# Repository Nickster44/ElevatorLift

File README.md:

# Elevator Lift Controller Redesign

This repository contains the Rev-A hardware design and inhibited software for a redesigned outdoor elevator lift controller. The original controller was a Particle Xenon sketch that drove an EM01 VFD over serial, watched a safety loop, counted position pulses in firmware, stored floor positions in EEPROM, and exchanged simple serial messages with a secondary relay/input board.

The new design goals are:

- Make motion control deterministic and auditable with an explicit state machine.
- Move encoder counting out of interrupt-heavy application code and into a quadrature counter IC.
- Store current position, floor targets, calibration values, faults, and event logs in nonvolatile MRAM.
- Host a local access-point web interface for setup, diagnostics, data logs, and maintenance actions, with optional station-mode connection to a local network.
- Keep safety functions electrically independent from the MCU wherever possible.
- Develop the custom controller board alongside a versioned firmware interface contract.

Important: this repository is not a certified elevator controller. The software here is a development baseline. Any real lift must use appropriately rated safety devices, hardwired interlocks, braking/enable circuits, limit switches, emergency stop hardware, enclosure design, and professional review before operation.

## Software Integration Status (2026-09-13)

The active software is a **buildable but hardware-inhibited N16R8 profile**.
GPIO35-37 are unavailable on this module. The 2026-09-13 hardware update moves
LIMIT_UP/LIMIT_DOWN/SERVICE_KEY to GPIO43/44/3 and makes GPIO42 a communications-only
UART enable, removing the MCU RUN and optional AUX circuits. Software contract v2
now adopts this revision. GPIO3 is input-only, UART0 application logging is disabled,
and UART1 supports STOP/monitor/readback while safety is open. RUN, drive writes,
motion and uploads remain inhibited. Stable input levels do not prove wire continuity.
No physical motion or hardware verification has been performed.

VFD communication now includes periodic STOP refresh (300 ms scheduled interval),
monitor/read traffic, and a separate bounded reply-retry policy. The drive's TIME
watchdog is read and reported, never automatically changed; communication failure
keeps STOP refresh active without restarting motion or clearing faults.

The manual-release STOP path is now target-bound: key/hold/direction release or
invalid direction/safety input queues STOP before ordinary work. Input intent is
reported separately from actual motion permission. The requested operational v3
profile, RF programming and calibration expansion are not complete; v2 remains inhibited.

See the [hardware change and routing handoff](docs/reviews/2026-09-13-pin-comms-fourlayer.md).
The PCB is synchronized and has four copper layers, but remains unrouted and
not layout-release/fabrication ready; isolation keepouts and fabricator-specific
stackup/USB geometry still need completion.

Start with the [software integration checklist](docs/software-integration-checklist.md),
[hardware-dependency handoff](docs/hardware-dependency-handoff.md),
[firmware guide](firmware/README.md) and [current API contract](webapp/docs/api-contract.md).
Portable motion/protocol/device logic has regression tests; target commissioning,
RF integration and several guarded API workflows remain incomplete. The WebUI
shows unavailable capabilities instead of simulating successful hardware actions.

## Current Repository Layout

Use the [documentation guide](docs/README.md) to distinguish current design
guidance from dated reviews and historical evidence.

```text
_old_resources/
  old_code.ino.txt                 Original Particle Xenon firmware
  EM01 Manual User_EN-V1.02.pdf     VFD manual; serial protocol starts on page 27
  SKF-Motor-Encoder-Unit---15276_1-EN.pdf
docs/
  hardware-requirements-matrix.md   Schematic-facing hardware requirements
  hardware-selection.md             Selected Rev-A hardware
  home-automation-integration.md    Local REST/Home Assistant/Google Home bridge plan
  jlcpcb-lcsc-sourcing.md           JLCPCB/LCSC-oriented major part matrix
  motion-control-and-calibration.md Motion strategy and measured stop calibration
  old-system-review.md              Existing firmware/hardware behavior and risks
  vfd-serial-protocol.md            Extracted EM01 serial protocol notes
  new-controller-requirements.md    Hardware and firmware requirements draft
  webui-vfd-and-storage-plan.md     WebUI, VFD parameter, and log storage plan
  webapp-embedded-delivery.md       ESP32 static bundle budget and serving rules
  field-verification-log.md         Observed legacy hardware and remaining site checks
  schematic-capture-readiness.md    Rev-A capture inputs, BOM register, and release gates
datasheets/
  README.md                         Local datasheet manifest for major ICs/modules
firmware/
  platformio.ini                    Inhibited N16R8 PlatformIO target
  include/
  src/
webapp/
  app/                              Full development and service-console UI
  embedded/                         Static entry point for the ESP32 build
  docs/                             WebUI API, safety, and delivery contracts
hardware/
  ElevatorLift.kicad_pro            KiCad 10 project; open this file
  ElevatorLift.kicad_sch            Root hierarchical schematic
  Power_RevA.kicad_sch              AC input and 12 V/5 V/3.3 V power
  MCU_Storage_RevA.kicad_sch        ESP32-S3, USB, MRAM and RTC
  VFD_Interface_RevA.kicad_sch      VFD UART and communications-only OE
  Encoder_Counter_RevA.kicad_sch    Encoder isolation and counter
  IO.kicad_sch                      RF, field inputs and outputs
  ElevatorLift.kicad_pcb            PCB WIP; full footprint/net transfer on a 90 mm x 90 mm outline with 86 mm hole centers
  ElevatorLift_Custom.kicad_sym     Project-owned symbols
  ElevatorLift_Custom.pretty/       Project-owned footprints
  SnapEDA-Library/                  Vendored imported symbols, footprints and STEP files
  sym-lib-table / fp-lib-table      Portable project library registrations
  architecture-blocks.md            Block-level hardware architecture notes
```

## Current Design Knowledge

The current hardware direction is an `ESP32-S3-WROOM-1U-N16R8` controller board in the VFD enclosure, using a self-hosted Wi-Fi AP as the primary service path and optional station Wi-Fi for local-network access. Ethernet is not a near-term requirement.

Known design constraints captured so far:

- KiCad 10.0.4 is the active hardware design version.
- Measured legacy mechanical target is approximately 90 mm x 90 mm with corner mounting-hole centers 86 mm apart; 2.56 mm hole diameter remains to be confirmed.
- The Rev-A VFD serial circuit has been cross-checked against the field design and reproduces its TI `TXS0104E` 3.3 V-to-5 V topology. The assembled board, connector pinout, reference, and idle levels still require bench verification before lift connection.
- The observed encoder path appears to be 12 V open-collector A/B with 270 ohm pullups and 270 ohm series resistors feeding a `TLP291-4` optocoupler. Trace details, current, and maximum pulse rate remain open.
- Legacy Linx/TE RXM-418-LR 418 MHz RF remote support is mandatory.
- Baseline control supply is RECOM `RAC10-12SK/277`, 12 V, 10 W, based on the previously observed installation; `C5199922` is a recorded sourcing reference, not verified current availability.
- Rev A retains a jumper-selectable external 12 V lighting input. Use it if measured controller margin is insufficient or future lighting requires more power than the onboard supply can provide.
- Critical state and recent logs should use 4 Mbit SPI/QPI MRAM, using the selected Siproin `PM004MNIATR`.
- Web assets, OTA staging and noncritical logs should use the module's 16 MB flash and 8 MB PSRAM first. Rev A does not include a separate QSPI NOR device.
- Outside control should use local REST first, optional MQTT later, and Home Assistant as the recommended bridge to Google Home, watches, and broader automation.
- Motion control should use measured deceleration-distance stopping, not PID. Planned calibration starts explicitly after valid floor programming and stores direction-specific offsets; target integration remains incomplete.

## Legacy Reference

The original pin map, behavior and risk analysis are retained in
[old-system-review.md](docs/old-system-review.md). They are historical evidence,
not wiring or operating instructions for Rev A.

## Firmware Direction

The firmware targets the exact N16R8 module using Arduino/PlatformIO and a versioned hardware interface contract. Portable core logic is tested separately from target adapters. A successful build is not permission to deploy.

Key modules:

- `core/Supervisor`: fault-latched motion, service, homing and measured calibration logic.
- `core/Em01`, `DriveScheduler`: framed/checksummed transactions, telemetry and readback.
- `core/Devices`, `Configuration`: LS7366R, PM004 MRAM, RTC and integrity-checked records.
- `core/Rf`: isolated learned-slot/epoch and input arbitration logic.
- `main.cpp`: inhibited target diagnostics, light output, networking and static hosting.
- `interface-contract.json`: confirmed pins and explicit unresolved hardware decisions.

## Local Web Interface/API

The firmware hosts static WebUI assets on port 80 and a fallback AP. Station credentials can be saved, but remote reboot is deliberately unsupported in the inhibited profile. Failed/lost station connectivity restores AP access. Blank API tokens disable writes.

Endpoints:

- `GET /` - embedded WebUI; no automatic demo mode.
- `GET /api/status` - versioned status, capabilities, blocked reasons and freshness.
- `GET /api/capabilities` - explicit supported capabilities.
- `GET /api/network` - current AP/station network status.
- `POST /api/network` - save station SSID/password and require a reboot.
- `POST /api/light` - idempotent light output command.
- `GET /api/logs/recent` - bounded durable MRAM events, unavailable on storage failure.
- `GET /api/vfd/parameters` - list documented VFD parameter metadata.
- `POST /api/move?floor=N` - strict input validation, then hardware-inhibited rejection.
- `POST /api/stop` - queues diagnostic STOP (202), or reports unavailable UART (503); neither transmission nor acknowledgement proves physical stopping.

Other commissioning, parameter-write, RF, restore and reboot endpoints are explicitly unsupported. See the API contract for remaining work; no UI capability implies hardware verification.

Fallback AP credentials are configured from `firmware/include/Secrets.h`, which is ignored by Git. Station network credentials are saved through the local web API.

Planned WebUI expansion includes local lift settings, RF pairing, VFD parameter read/write, current-limit/load-limit tuning, configuration backup/restore, and log export.

The preferred home-automation path is local REST API first, optional MQTT later, and Home Assistant as the bridge to Google Home. Google Home should not talk directly to the lift controller or bypass the controller's authentication, logging, and motion prechecks.

## Captured Hardware Architecture

The Rev-A design contains the following blocks; physical qualification remains open:

- Exact `ESP32-S3-WROOM-1U-N16R8` external-antenna Wi-Fi module.
- Fused 120 VAC + neutral input, isolated 12 V supply, 5 V rail, and 3.3 V rail.
- VFD UART interface reproducing the field-used 3.3 V-to-5 V `TXS0104E` topology, with an assembled-board bench gate before lift connection.
- LS7366R SPI quadrature counter.
- Encoder input conditioning for the observed 12 V open-collector quadrature outputs, including isolation/level translation before the counter.
- SPI MRAM for live position snapshots, settings, recent event logs, and fault records.
- The selected N16R8 module's 16 MB flash and 8 MB PSRAM serve WebUI assets, OTA staging and noncritical data; no separate Rev-A QSPI device is planned.
- Hardware safety chain independent of application firmware.
- External hardwired motion authority; GPIO42 enables UART translation only, not RUN or a brake.
- Protected digital inputs for call buttons, RF receiver, limit switches, home switch, and safety loop.
- Mandatory RXM-418-LR RF receiver path.
- Protected 12 V MOSFET light output with jumper-selectable onboard or external 12 V supply. AUX has been removed.
- Watchdog and brownout detection.
- Surge/ESD/EMI protection suitable for outdoor wiring and a VFD enclosure.

The service/recovery interface uses dry-contact inputs: J43 provides SERVICE
KEY, HOLD-TO-RUN and GND; J44 provides SERVICE UP, SERVICE DOWN and GND. The
intended external hardware is a maintained keyed service switch, a momentary
hold-to-run control, and momentary UP/DOWN controls. These optocoupler-conditioned, shared-ground
MCU inputs are authorization/command inputs only; they are not a safety-rated
enabling circuit and may not bypass the independent emergency-stop, final-limit,
watchdog or VFD motion-authority paths.

## Opening The Hardware Project On Another Computer

Clone or copy the complete repository and open `hardware/ElevatorLift.kicad_pro`
with KiCad 10. The custom and SnapEDA libraries are stored under `hardware/` and
registered through `${KIPRJMOD}` paths, so no `D:\Downloads` or user-profile
library path is required. Do not copy only the `.kicad_pro` file: the five child
schematics, board, project library tables, custom libraries and vendored
SnapEDA library directory must remain together.

## Physical Verification Checklist

The initial on-site observations are recorded in `docs/field-verification-log.md`.
Before hardware release, complete the remaining checks below. The
[external-box evidence checklist](docs/reviews/2026-09-13-manual-control-box.md)
defines the non-energized wiring review; this list does not authorize live testing.

1. Confirm the estimated 40 mm enclosure height and 12 mm underside clearance, then measure connector/wire-bend keepouts and airflow.
2. Confirm the approximately 90 mm x 90 mm board, 86 mm mounting-hole centers, 2.56 mm hole diameter, screw size, and standoff material.
3. Old controller hardware: photograph both sides of the Particle/Xenon board and accessory Nano board, record IC markings, regulator parts, RF receiver wiring, level-shifting parts, optocouplers, drivers, relay part numbers, fuses, MOVs, terminal blocks, and any bodge wiring.
4. VFD serial interface: verify the field-matched `TXS0104E` circuit on the assembled board, including header pinout, idle voltage, common/reference, polarity, receive level, cable length, and bench behavior.
5. Power input: where 120 VAC can be tapped, whether it is upstream/downstream of the disconnect, available neutral, protective earth/chassis connection, fuse location, wire gauge, and connector style.
6. Existing 12 V loads: light voltage/current, inrush behavior, shared return path, connector type, and whether any solenoid/interlock output still needs power.
7. Encoder wiring: verify the observed 12 V supply, 270 ohm pullups, 270 ohm series resistors, `TLP291-4` path, exact encoder model, A/B idle voltage, cable/shielding, connector pinout, and maximum pulse rate.
8. Button, home, limit, and safety wiring: voltage levels, normally-open/normally-closed behavior, whether contacts are dry or powered, cable routing, and what is hardwired versus MCU-only.
9. RF system: confirm receiver module marking, antenna type/location, data output idle level, remote count, remote mapping, pairing behavior, and the separate wired `LEARN` node.
10. Grounding and EMI: cabinet earth strategy, shield terminations, VFD motor lead routing, separation between mains/motor wiring and control wiring, and any existing noise filters.
11. VFD parameters: dump or photograph current drive parameters, especially acceleration, deceleration, max frequency, current/overload settings, serial timeout, and any stop/enable terminal configuration.
12. Safety devices: identify final limits, emergency stop, gate/latch devices, brakes, and any non-MCU circuits that remove motion authority.

## Remaining Software Work

Drivers, integrity-checked MRAM records, token authentication and host protocol
simulations exist. Track remaining operational motion, RF capture/programming,
explicit calibration, guarded settings and update workflows in the
[integration checklist](docs/software-integration-checklist.md).

## Build Firmware Without Deployment

Install PlatformIO, then run:

```powershell
cd firmware
pio run
```

Upload and uploadfs deliberately fail in this profile. See the
[firmware guide](firmware/README.md) for host tests and filesystem builds and the
[WebUI guide](webapp/README.md) for mocked browser tests. Do not remove the inhibit
to try hardware; physical qualification remains separate.

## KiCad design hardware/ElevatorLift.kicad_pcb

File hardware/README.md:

# Hardware / KiCad Workspace

This folder is the hardware design workspace. The KiCad 10 project now contains a Rev-A schematic capture and an unrouted four-layer PCB for review. It is not yet approved for PCB layout or manufacturing.

## Files

| File | Purpose |
| --- | --- |
| `ElevatorLift.kicad_pro` | KiCad project |
| `ElevatorLift.kicad_sch` | Root hierarchical schematic |
| `Power_RevA.kicad_sch` | Fused AC input and isolated 12 V, 5 V and 3.3 V rails |
| `MCU_Storage_RevA.kicad_sch` | ESP32-S3, USB, MRAM, RTC and service interfaces |
| `VFD_Interface_RevA.kicad_sch` | 3.3 V/5 V UART translation; communications-only enable, no MCU RUN output |
| `Encoder_Counter_RevA.kicad_sch` | Isolated encoder inputs and LS7366R counter |
| `IO.kicad_sch` | Linx RF, monitored field inputs and light output; optional AUX removed |
| `ElevatorLift.kicad_pcb` | PCB work-in-progress: 90 mm x 90 mm outline, 86 mm corner-hole centers, and the complete schematic footprint/net transfer |
| `ElevatorLift_Custom.kicad_sym` / `ElevatorLift_Custom.pretty` | Project-owned custom symbols and corrected/provisional footprints |
| `SnapEDA-Library` | Repository-owned copy of imported symbols, footprints and supplied STEP files |
| `sym-lib-table` / `fp-lib-table` | Project library registrations using portable `${KIPRJMOD}` paths |
| `architecture-blocks.md` | Schematic page/block plan |

## Current Schematic Pages

1. Root hierarchy and design notes.
2. Power (`Power_RevA`).
3. MCU and storage (`MCU_Storage_RevA`).
4. VFD interface (`VFD_Interface_RevA`).
5. Encoder counter (`Encoder_Counter_RevA`).
6. Consolidated RF, field inputs and outputs (`IO`).

The superseded standalone RF, safety, output and connector child sheets were
removed after their contents were consolidated into the active Rev-A hierarchy.

## Rev-A Capture Assumptions

Use [the hardware requirements matrix](../docs/hardware-requirements-matrix.md) and the main README physical verification checklist as the source of truth. The current schematic assumptions are:

- Target PCB outline: 90 mm x 90 mm; corner mounting-hole centers 86 mm apart. The reported 12 mm underside and approximately 40 mm upper clearances are enclosure estimates, not defined keepout radii. Verify screw-head/standoff envelopes and the estimated 2.56 mm hole diameter before layout release.
- Main supply: fused 120 VAC + neutral to exact RECOM `RAC10-12SK/277`; protected 12 V distribution uses `MF-MSMF075/24X`; 5 V uses an `R-78E5.0-0.5`; and 3.3 V uses an AP63203 stage with Bourns `SRP7028A-2R2M`.
- 5 V source sharing: separate `LM66100DCKR` ideal diodes isolate the onboard 5 V converter and USB VBUS before they join the 5 V rail. USB VBUS alone does not power the separate 3.3 V regulator; an approved bench-power procedure remains necessary.
- VFD serial: the `TXS0104E` circuit matches the field design, with the `TSW-104-07-G-S` header ordered 5 V, GND, RX, TX. Assembled-board pinout and bench behavior remain release gates.
- Encoder: 12 V field inputs use 2.2 kOhm LED resistors into `TLP291-4` isolation. This intentionally replaces the observed legacy 270 ohm values to avoid excessive optocoupler current; verify reliable switching on the actual encoder.
- RF: RXM-418-LR and `LICAL-DEC-MS001` support is mandatory; include a separate wired `LEARN` interface plus a local service button/pads.
- Light output: protected 12 V MOSFET output with an onboard/external supply selector. The previous 750 mA lighting operated from the 10 W RAC10 supply; verify Rev-A load margin, and select the external 12 V lamp input if controller demand or upgraded lighting exceeds the onboard budget.
- Service station: J43 accepts dry-contact SERVICE KEY and HOLD-TO-RUN inputs with a shared GND; J44 accepts dry-contact SERVICE UP and SERVICE DOWN inputs with a shared GND. Use a maintained key switch and momentary controls. These are optocoupler-conditioned MCU inputs sharing controller GND, not an independent galvanic barrier or a safety-rated enabling circuit.
- Current MCU assignment: LIMIT_UP GPIO43/module pin 37 through 1k R62; LIMIT_DOWN GPIO44/pin 36; SERVICE_KEY GPIO3/pin 15. GPIO35/36/37 remain NC for octal PSRAM. J11 UART pins 3/4 are now NC; use native USB. Preserve active-low inputs and default JTAG eFuses; see the reset/boot details in the current handoff.
- GPIO42 is VFD_COMMS_ENABLE and connects only U24 OE plus R24's 10k pulldown. R25/U25/J25/TP26 and AUX R59/R60/Q41/F41/D42/J47 are removed. The separate external hardwired safety loop remains the required RUN authority, subject to VFD configuration verification.

## PCB Preparation Status

- The current board contains 126 footprints (including four mounting holes) and 140 nets. The 90 x 90 mm outline runs from `(97.26,52.29325)` to `(187.26,142.29325)` mm. The four provisional 2.6 mm NPTH holes retain 86 mm spacing and a 2 mm offset from each adjacent edge.
- Net classes retain 3.2 mm mains clearance and 0.8 mm SELV power track width (0.2 mm clearance), plus the provisional USB differential-pair settings.
- The downloaded ESP32 module footprint contained invalid 0.2 mm plated holes. `ElevatorLift_Custom:ESP32-S3-WROOM-1U-N16R8_CorrectedV2` replaces it with the correct perimeter geometry and nine symbol-compatible exposed-pad segments.
- The provisional mains connector is now Phoenix Contact `1717732`, 7.62 mm pitch. The former 5 mm-pitch part could not satisfy the selected 3.2 mm mains clearance rule.
- Existing footprint positions and sides are preserved except for a local C23/C26 move that shortens U20's input/bootstrap loops; new R62 was also placed. Four layers are enabled: F.Cu, In1.Cu (SELV GND reference), In2.Cu (power/constrained signals), B.Cu. No tracks or zones were created. The nominal 1.6 mm board thickness is not a selected fabricator stackup.
- Current verification: ERC 0 errors/31 unchanged warnings; PCB DRC 325 unrouted errors, 181 warnings, no other errors, zero schematic parity findings. The final Konnect synchronization dry run is a no-op. These checks do not make the board layout-ready.
- See [the current handoff](../docs/reviews/2026-09-13-pin-comms-fourlayer.md) for exact pin mapping, prototype gates, placement concerns, all-layer isolation/antenna keepouts still to implement, and the provisional USB rule. Konnect's `.konnect/project.json` records routing guidance, not enforced KiCad custom rules.

Dated review results are evidence, not a live release status. See the
[external-box review](../docs/reviews/2026-09-13-manual-control-box.md) for the
latest field-interface evidence and unresolved independent stopping authority.

## Portable Project Libraries

Open `ElevatorLift.kicad_pro`, not an individual child sheet. Both project
library tables use `${KIPRJMOD}` paths:

- `SnapEDA` resolves to `hardware/SnapEDA-Library`.
- `ElevatorLift_Custom` resolves to the custom symbol file and footprint folder
  beside the project.

The repository-owned SnapEDA directory is a byte-for-byte copy of the imported
download and includes the supplied STEP files. Standard KiCad libraries are
still required, so install KiCad 10 with its normal symbol and footprint
packages on the destination computer.

See [field observations](../docs/field-verification-log.md) and the
[capture register](../docs/schematic-capture-readiness.md) for the confirmed observations, reusable-parts register, and the remaining release gates.

## KiCad Tooling

This project is pinned to KiCad 10.0.4. Use `tools\kicad.ps1` rather than a
generic `kicad-cli` command so automated checks do not accidentally run against
the also-installed KiCad 8 version.

```powershell
# From the repository root
powershell -ExecutionPolicy Bypass -File hardware\tools\kicad.ps1 -Action Version
powershell -ExecutionPolicy Bypass -File hardware\tools\kicad.ps1 -Action Validate
powershell -ExecutionPolicy Bypass -File hardware\tools\kicad.ps1 -Action Gui
```

`Validate` writes KiCad-native ERC and DRC JSON reports to `hardware\reports`
by default. The reports are generated design-review artifacts and should be
regenerated whenever the schematic or board changes.

The helper scripts auto-detect conventional OneDrive/Documents KiCad plugin
locations. On a different layout, set `KONNECT_PLUGIN_ROOT` to the installed
Konnect directory and `KICAD_10_BIN` to the KiCad 10 `bin` directory. Neither
environment variable is required merely to open and edit the project in KiCad.
Use PowerShell 7 for the Konnect batch helper; the basic KiCad launcher also
supports Windows PowerShell 5.1.

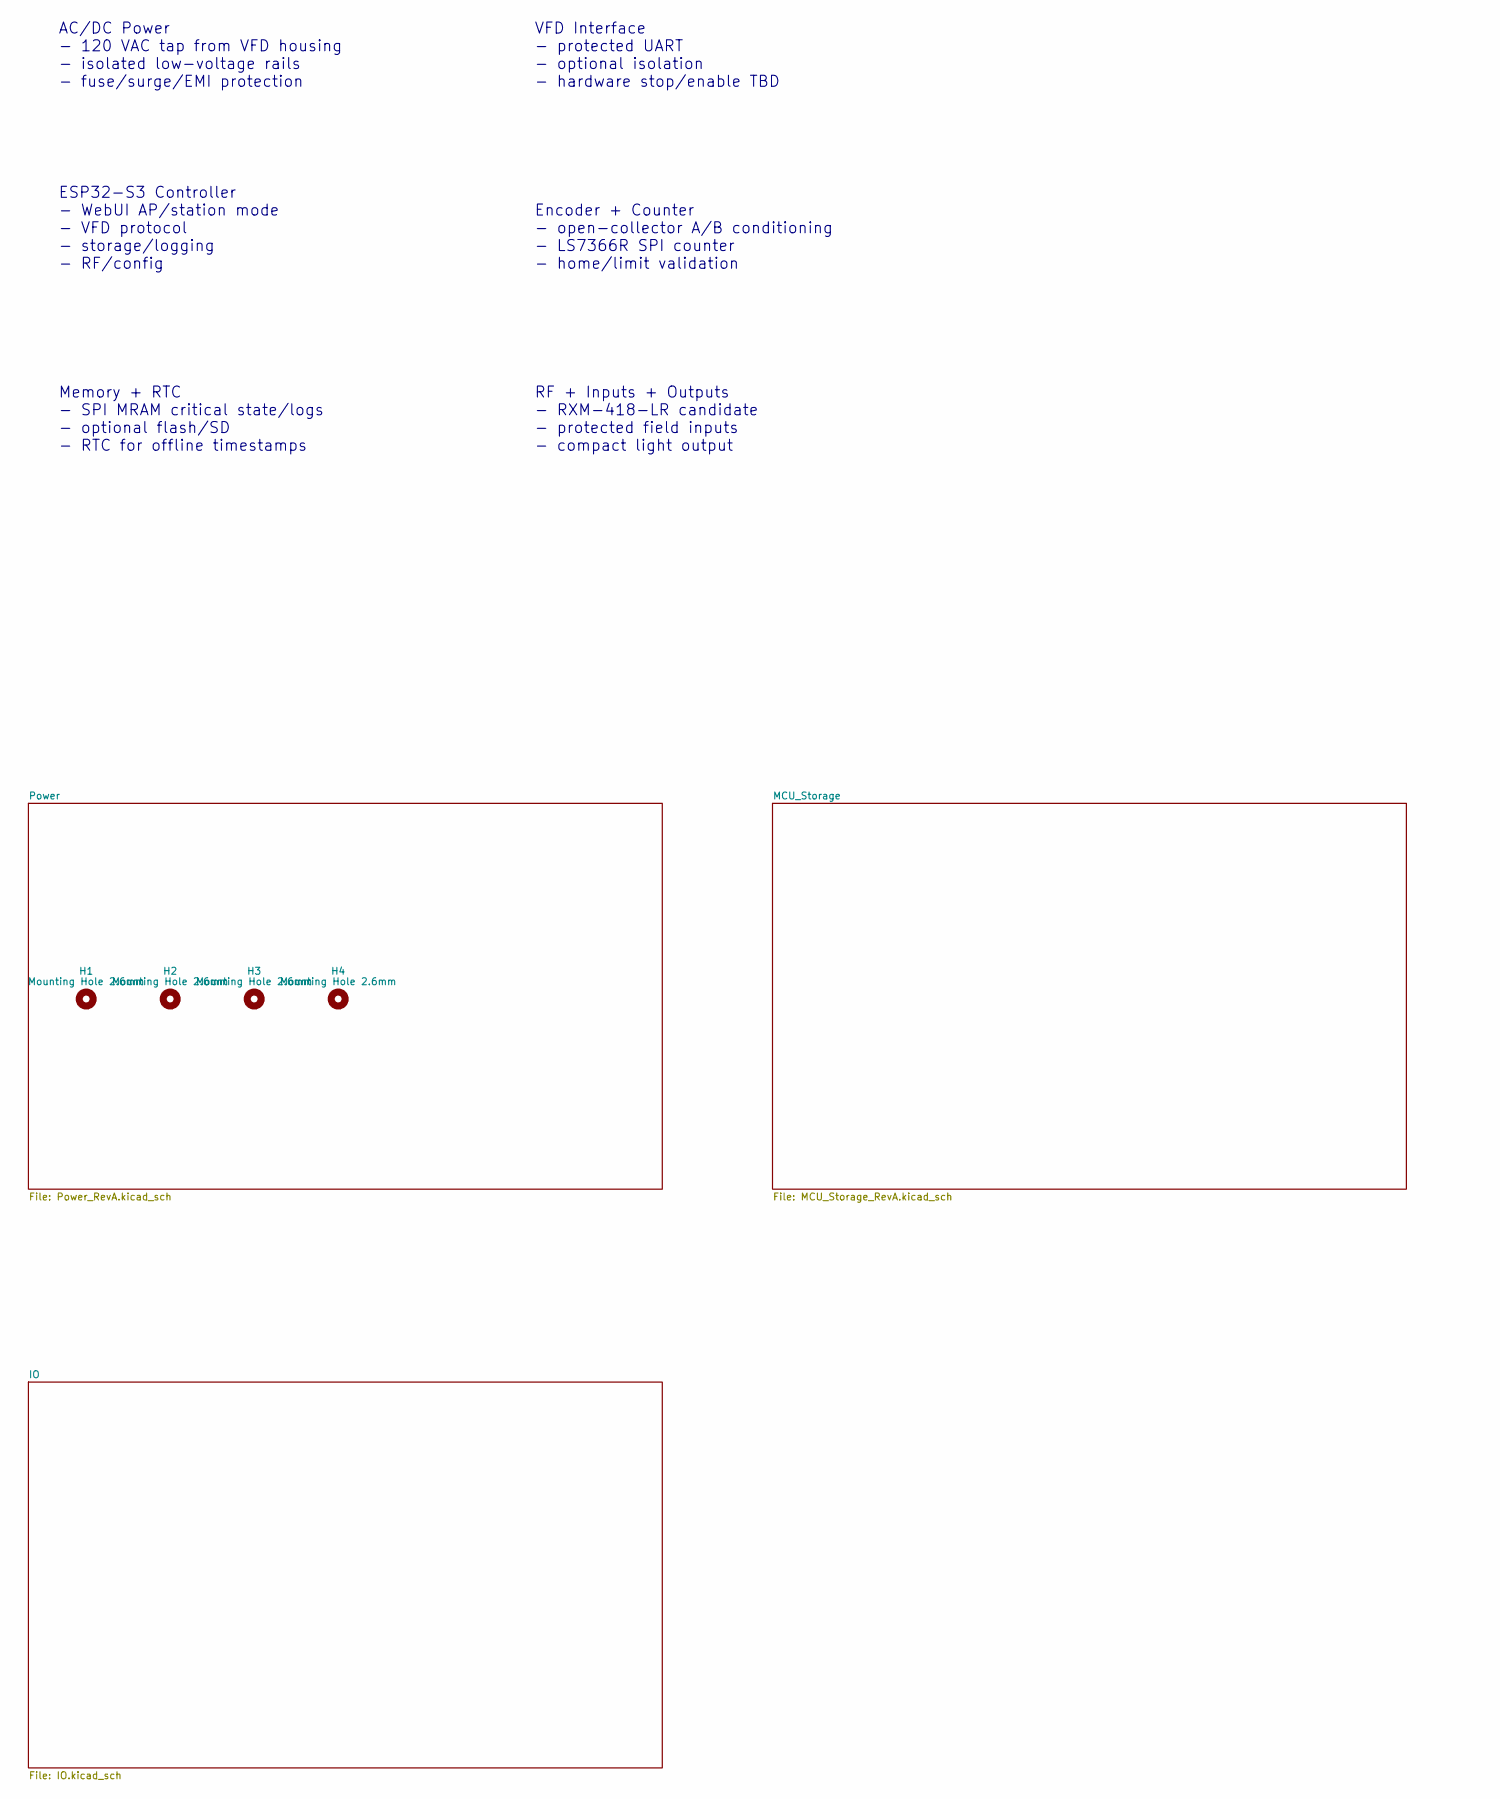
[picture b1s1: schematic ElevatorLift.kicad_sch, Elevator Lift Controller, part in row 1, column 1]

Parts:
H1, H2, H3, H4: Mounting Hole 2.6mm; MountingHole_2.6mm_NPTH

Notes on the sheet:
ESP32-S3 Controller - WebUI AP/station mode - VFD protocol - storage/logging - RF/config
RF + Inputs + Outputs - RXM-418-LR candidate - protected field inputs - compact light output
AC/DC Power - 120 VAC tap from VFD housing - isolated low-voltage rails - fuse/surge/EMI protection
VFD Interface - protected UART - optional isolation - hardware stop/enable TBD
Memory + RTC - SPI MRAM critical state/logs - optional flash/SD - RTC for offline timestamps
Encoder + Counter - open-collector A/B conditioning - LS7366R SPI counter - home/limit validation

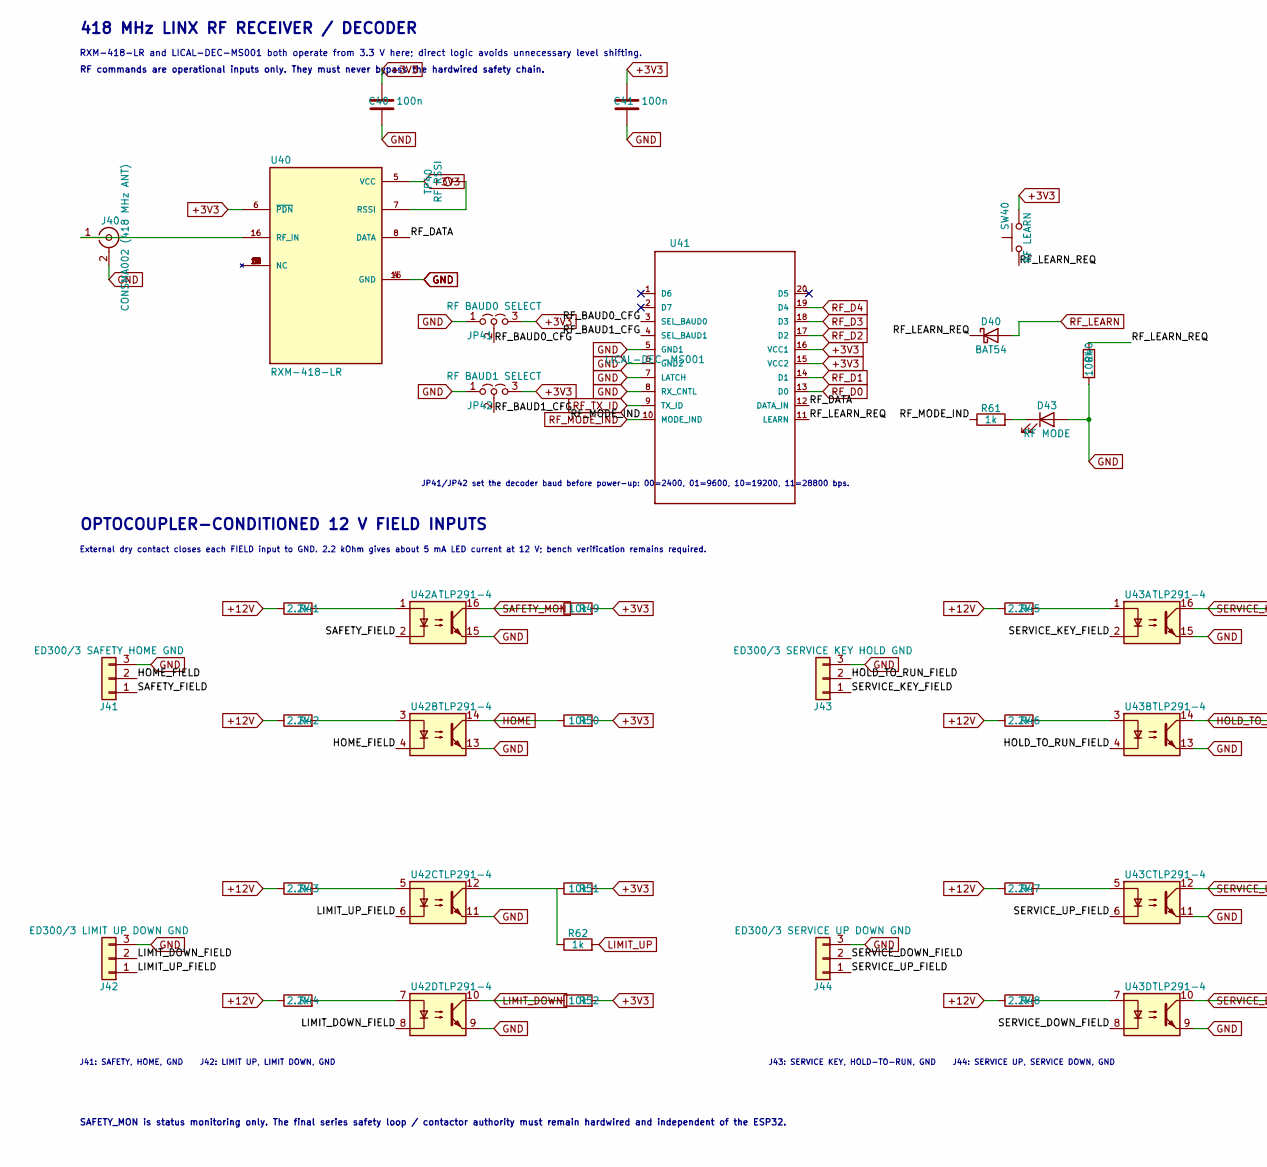
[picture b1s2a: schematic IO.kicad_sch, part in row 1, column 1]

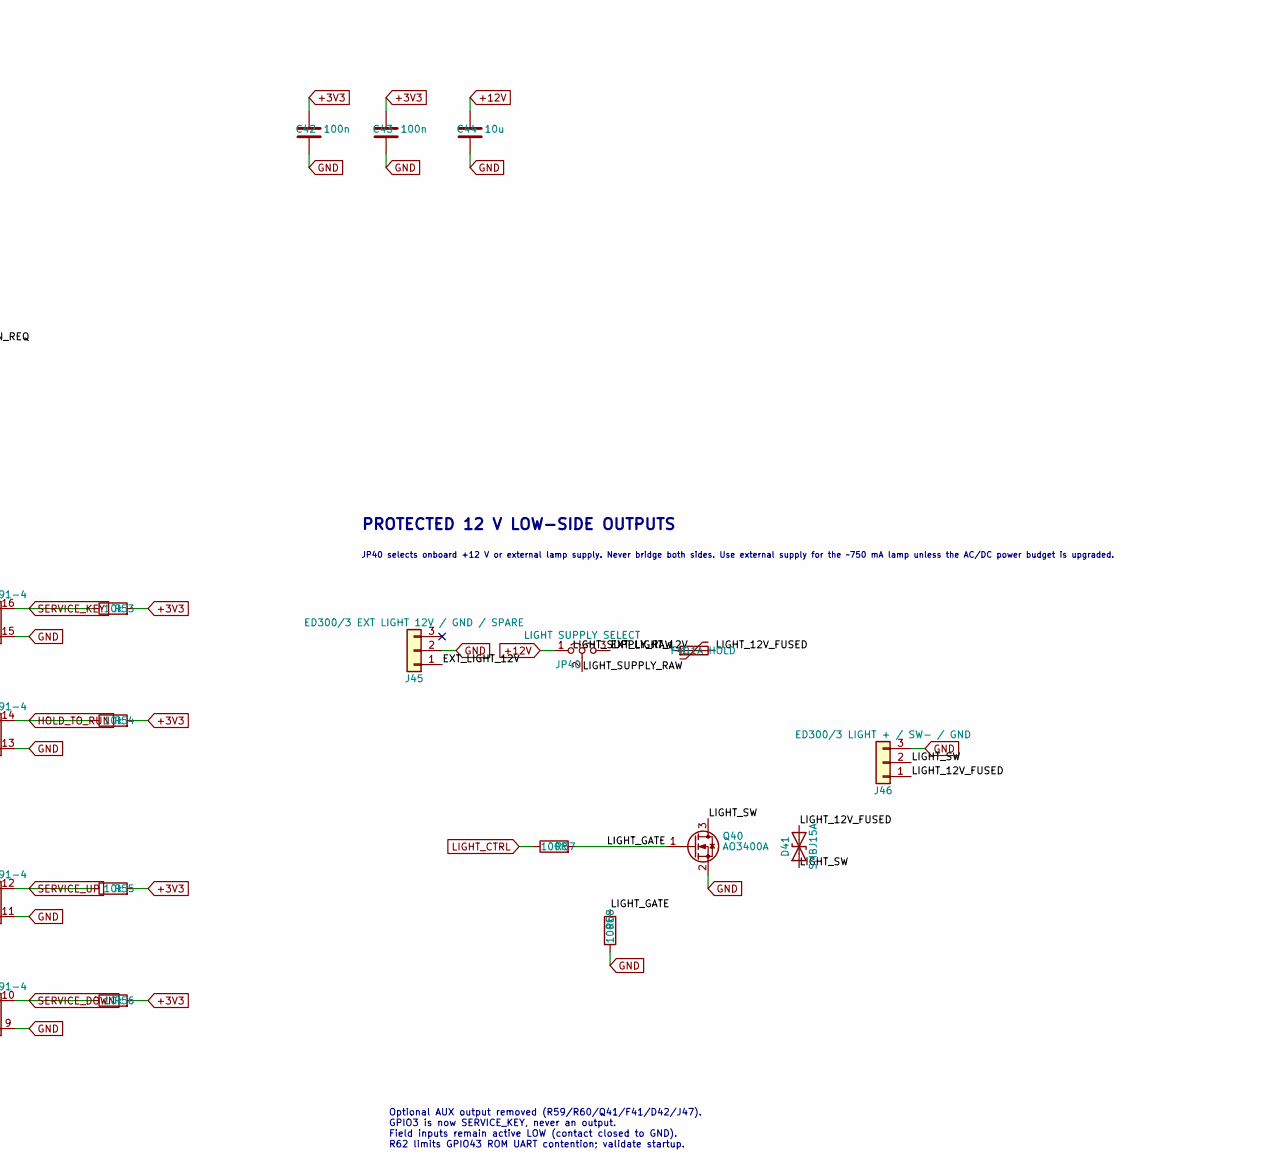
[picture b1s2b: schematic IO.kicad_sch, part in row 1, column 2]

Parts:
C40, C41, C42, C43: 100n; C_0603_1608Metric
C44: 10u; C_0805_2012Metric
D40: BAT54; D_SOD-323
D41: SMBJ15A; D_SMA
D43: RF MODE; LED_0603_1608Metric
F40: 1.1A HOLD; Fuse_1812_4532Metric
J40: CONSMA002 (418 MHz ANT); SMA_TE-Linx_CONSMA002_RightAngle
J41: ED300/3 SAFETY HOME GND; Altech_AK300_1x03_P5.00mm_45-Degree
J42: ED300/3 LIMIT UP DOWN GND; Altech_AK300_1x03_P5.00mm_45-Degree
J43: ED300/3 SERVICE KEY HOLD GND; Altech_AK300_1x03_P5.00mm_45-Degree
J44: ED300/3 SERVICE UP DOWN GND; Altech_AK300_1x03_P5.00mm_45-Degree
J45: ED300/3 EXT LIGHT 12V / GND / SPARE; Altech_AK300_1x03_P5.00mm_45-Degree
J46: ED300/3 LIGHT + / SW- / GND; Altech_AK300_1x03_P5.00mm_45-Degree
JP40: LIGHT SUPPLY SELECT; PinHeader_1x03_P2.54mm_Vertical
JP41: RF BAUD0 SELECT; PinHeader_1x03_P2.54mm_Vertical
JP42: RF BAUD1 SELECT; PinHeader_1x03_P2.54mm_Vertical
Q40: AO3400A; SOT-23
R40, R58: 100k; R_0603_1608Metric
R41, R42, R43, R44, R45, R46, R47, R48: 2.2k; R_0603_1608Metric
R49, R50, R51, R52, R53, R54, R55, R56: 10k; R_0603_1608Metric
R57: 100R; R_0603_1608Metric
R61, R62: 1k; R_0603_1608Metric
SW40: RF LEARN; SW_SPST_PTS810
TP40: RF RSSI; TestPoint_Pad_D1.0mm
U40: RXM-418-LR; XCVR_RXM-418-LR; MPN RXM-418-LR
U41: LICAL-DEC-MS001; 20-SSOP; MPN LICAL-DEC-MS001
U42, U43: TLP291-4; SOIC-16_4.55x10.3mm_P1.27mm; MPN TLP291-4

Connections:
+3V3: C40.1, C41.1, C42.1, C43.1, JP41.3 (B), JP42.3 (B), R49.2, R50.2, R51.2, R52.2, R53.2, R54.2, R55.2, R56.2, SW40.2, U40.5 (VCC), U40.6 (~PDN), U41.15 (VCC2), U41.16 (VCC1); also elsewhere on the board
+12V: C44.1, JP40.1 (A), R41.1, R42.1, R43.1, R44.1, R45.1, R46.1, R47.1, R48.1; also elsewhere on the board
/IO/EXT_LIGHT_12V: J45.1, JP40.3 (B)
/IO/HOLD_TO_RUN_FIELD: J43.2, U43.4
/IO/HOME_FIELD: J41.2, U42.4
/IO/LIGHT_12V_FUSED: D41.2 (A2), F40.2, J46.1
/IO/LIGHT_GATE: Q40.1 (G), R57.2, R58.1
/IO/LIGHT_SUPPLY_RAW: F40.1, JP40.2 (C)
/IO/LIGHT_SW: D41.1 (A1), J46.2, Q40.3 (D)
/IO/LIMIT_DOWN_FIELD: J42.2, U42.8
/IO/LIMIT_UP_FIELD: J42.1, U42.6
/IO/RF_BAUD0_CFG: JP41.2 (C), U41.3 (SEL_BAUD0)
/IO/RF_BAUD1_CFG: JP42.2 (C), U41.4 (SEL_BAUD1)
/IO/RF_DATA: U40.8 (DATA), U41.12 (DATA_IN)
/IO/RF_LEARN_REQ: D40.1 (K), R40.1, SW40.1, U41.11 (LEARN)
/IO/SAFETY_FIELD: J41.1, U42.2
/IO/SERVICE_DOWN_FIELD: J44.2, U43.8
/IO/SERVICE_KEY_FIELD: J43.1, U43.2
/IO/SERVICE_UP_FIELD: J44.1, U43.6
GND: C40.2, C41.2, C42.2, C43.2, C44.2, D43.2 (A), J40.2 (Ext), J41.3, J42.3, J43.3, J44.3, J45.2, J46.3, JP41.1 (A), JP42.1 (A), Q40.2 (S), R40.2, R58.2, U40.4 (GND), U40.15 (GND), U41.5 (GND1), U41.6 (GND2), U41.7 (LATCH), U41.8 (RX_CNTL), U42.9, U42.11, U42.13, U42.15, U43.9, U43.11, U43.13, U43.15; also elsewhere on the board
HOLD_TO_RUN: R54.1, U43.14; also elsewhere on the board
HOME: R50.1, U42.14; also elsewhere on the board
LIGHT_CTRL: R57.1; also elsewhere on the board
LIMIT_DOWN: R52.1, U42.10; also elsewhere on the board
LIMIT_UP: R62.2; also elsewhere on the board
unnamed: D43.1 (K), R61.2
unnamed: J40.1 (In), U40.16 (RF_IN)
unnamed: R41.2, U42.1
unnamed: R42.2, U42.3
unnamed: R43.2, U42.5
unnamed: R44.2, U42.7
unnamed: R45.2, U43.1
unnamed: R46.2, U43.3
unnamed: R47.2, U43.5
unnamed: R48.2, U43.7
unnamed: R51.1, R62.1, U42.12
unnamed: TP40.1 (1_1), U40.7 (RSSI)
RF_D0: U41.13 (D0); also elsewhere on the board
RF_D1: U41.14 (D1); also elsewhere on the board
RF_D2: U41.17 (D2); also elsewhere on the board
RF_D3: U41.18 (D3); also elsewhere on the board
RF_D4: U41.19 (D4); also elsewhere on the board
RF_LEARN: D40.2 (A); also elsewhere on the board
RF_MODE_IND: R61.1, U41.10 (MODE_IND); also elsewhere on the board
RF_TX_ID: U41.9 (TX_ID); also elsewhere on the board
SAFETY_MON: R49.1, U42.16; also elsewhere on the board
SERVICE_DOWN: R56.1, U43.10; also elsewhere on the board
SERVICE_KEY: R53.1, U43.16; also elsewhere on the board
SERVICE_UP: R55.1, U43.12; also elsewhere on the board

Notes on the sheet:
418 MHz LINX RF RECEIVER / DECODER
J43: SERVICE KEY, HOLD-TO-RUN, GND J44: SERVICE UP, SERVICE DOWN, GND
OPTOCOUPLER-CONDITIONED 12 V FIELD INPUTS
PROTECTED 12 V LOW-SIDE OUTPUTS
RF commands are operational inputs only. They must never bypass the hardwired safety chain.
External dry contact closes each FIELD input to GND. 2.2 kOhm gives about 5 mA LED current at 12 V; bench verification remains required.
JP40 selects onboard +12 V or external lamp supply. Never bridge both sides. Use external supply for the ~750 mA lamp unless the AC/DC power budget is upgraded.
SAFETY_MON is status monitoring only. The final series safety loop / contactor authority must remain hardwired and independent of the ESP32.
JP41/JP42 set the decoder baud before power-up: 00=2400, 01=9600, 10=19200, 11=28800 bps.
Optional AUX output removed (R59/R60/Q41/F41/D42/J47). GPIO3 is now SERVICE_KEY, never an output. Field inputs remain active LOW (contact closed to GND). R62 limits GPIO43 ROM UART contention; validate startup.
RXM-418-LR and LICAL-DEC-MS001 both operate from 3.3 V here; direct logic avoids unnecessary level shifting.
J41: SAFETY, HOME, GND J42: LIMIT UP, LIMIT DOWN, GND

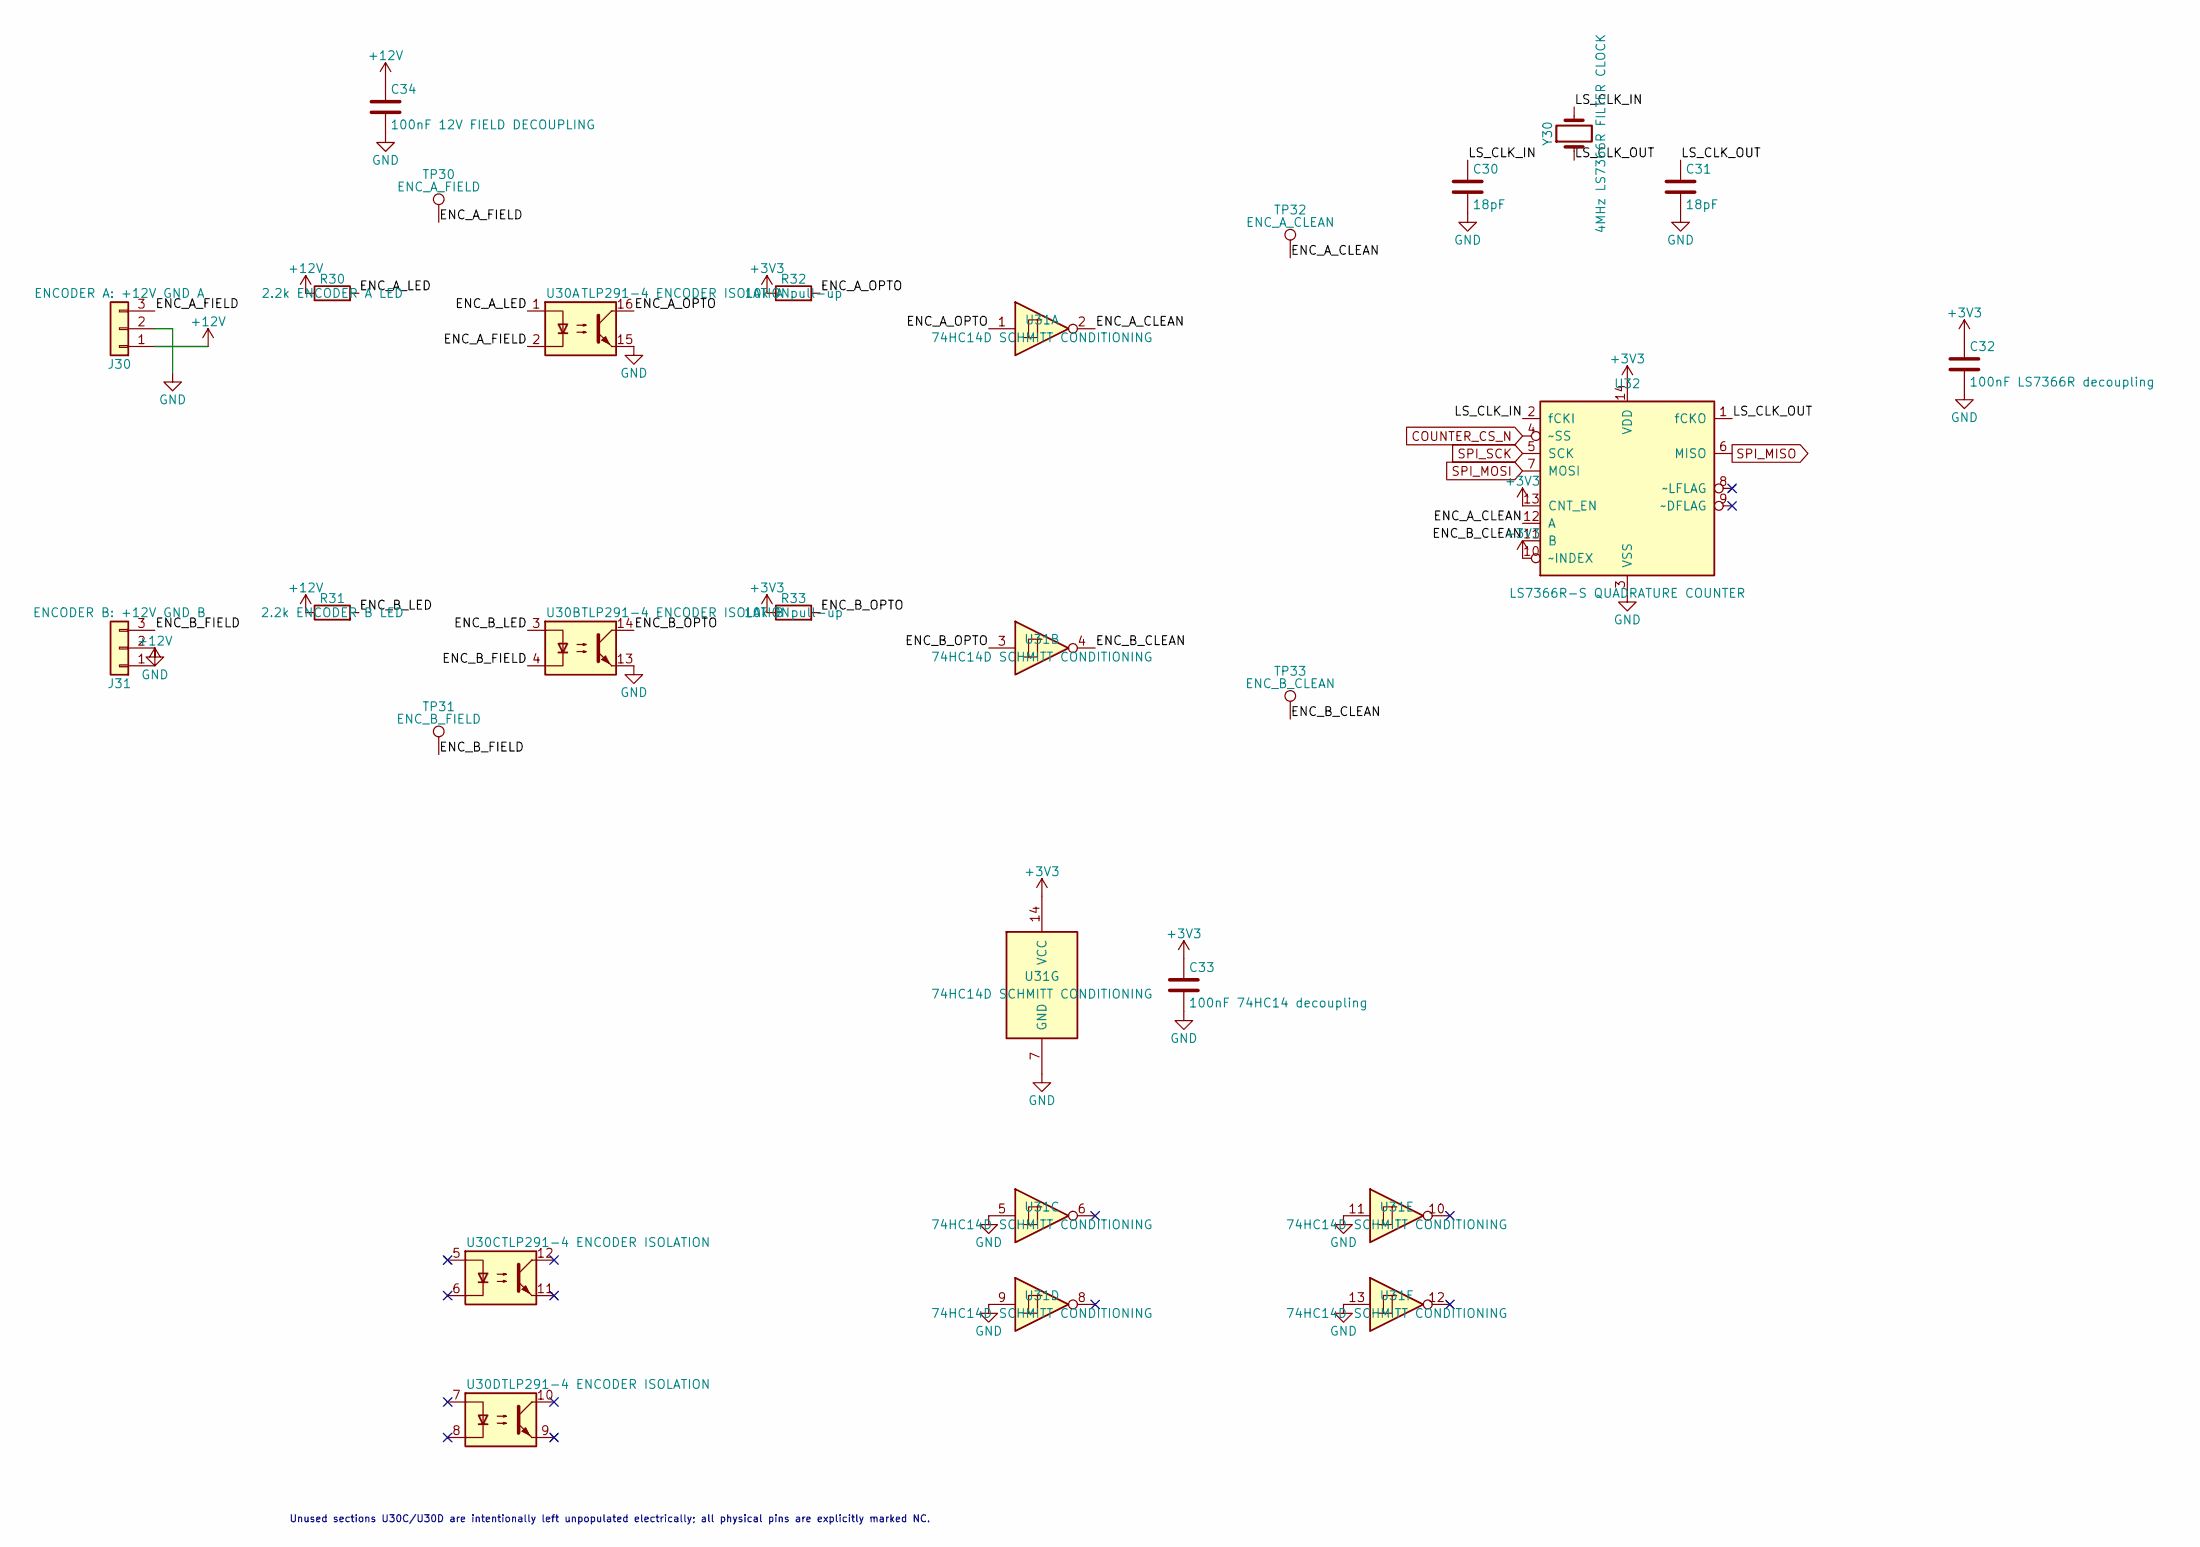
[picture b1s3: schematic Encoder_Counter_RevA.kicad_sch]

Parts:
C30, C31: 18pF; C_0603_1608Metric
C32: 100nF LS7366R decoupling; C_0603_1608Metric
C33: 100nF 74HC14 decoupling; C_0603_1608Metric
C34: 100nF 12V FIELD DECOUPLING; C_0603_1608Metric
J30: ENCODER A: +12V GND A; Altech_AK300_1x03_P5.00mm_45-Degree
J31: ENCODER B: +12V GND B; Altech_AK300_1x03_P5.00mm_45-Degree
R30: 2.2k ENCODER A LED; R_0603_1608Metric
R31: 2.2k ENCODER B LED; R_0603_1608Metric
R32: 10k A pull-up; R_0603_1608Metric
R33: 10k B pull-up; R_0603_1608Metric
TP30: ENC_A_FIELD; TestPoint_Pad_D1.0mm
TP31: ENC_B_FIELD; TestPoint_Pad_D1.0mm
TP32: ENC_A_CLEAN; TestPoint_Pad_D1.0mm
TP33: ENC_B_CLEAN; TestPoint_Pad_D1.0mm
U30: TLP291-4 ENCODER ISOLATION; SOIC-16_4.55x10.3mm_P1.27mm; MPN TLP291-4
U31: 74HC14D SCHMITT CONDITIONING; SOIC-14_3.9x8.7mm_P1.27mm; MPN 74HC14D,653
U32: LS7366R-S QUADRATURE COUNTER; SOIC-14_3.9x8.7mm_P1.27mm; MPN LS7366R-S
Y30: 4MHz LS7366R FILTER CLOCK; Crystal_SMD_3225-4Pin_3.2x2.5mm

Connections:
+3V3: C32.1, C33.1, R32.1, R33.1, U31.14 (VCC), U32.10 (~INDEX), U32.13 (CNT_EN), U32.14 (VDD); also elsewhere on the board
+12V: C34.1, J30.1, J31.1, R30.1, R31.1; also elsewhere on the board
/Encoder_Counter/ENC_A_CLEAN: TP32.1 (1_1), U31.2, U32.12 (A)
/Encoder_Counter/ENC_A_FIELD: J30.3, TP30.1 (1_1), U30.2
/Encoder_Counter/ENC_A_LED: R30.2, U30.1
/Encoder_Counter/ENC_A_OPTO: R32.2, U30.16, U31.1
/Encoder_Counter/ENC_B_CLEAN: TP33.1 (1_1), U31.4, U32.11 (B)
/Encoder_Counter/ENC_B_FIELD: J31.3, TP31.1 (1_1), U30.4
/Encoder_Counter/ENC_B_LED: R31.2, U30.3
/Encoder_Counter/ENC_B_OPTO: R33.2, U30.14, U31.3
/Encoder_Counter/LS_CLK_IN: C30.1, U32.2 (fCKI), Y30.2
/Encoder_Counter/LS_CLK_OUT: C31.1, U32.1 (fCKO), Y30.1
COUNTER_CS_N: U32.4 (~SS); also elsewhere on the board
GND: C30.2, C31.2, C32.2, C33.2, C34.2, J30.2, J31.2, U30.13, U30.15, U31.5, U31.7 (GND), U31.9, U31.11, U31.13, U32.3 (VSS); also elsewhere on the board
SPI_MISO: U32.6 (MISO); also elsewhere on the board
SPI_MOSI: U32.7 (MOSI); also elsewhere on the board
SPI_SCK: U32.5 (SCK); also elsewhere on the board

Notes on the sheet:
Unused sections U30C/U30D are intentionally left unpopulated electrically; all physical pins are explicitly marked NC.
